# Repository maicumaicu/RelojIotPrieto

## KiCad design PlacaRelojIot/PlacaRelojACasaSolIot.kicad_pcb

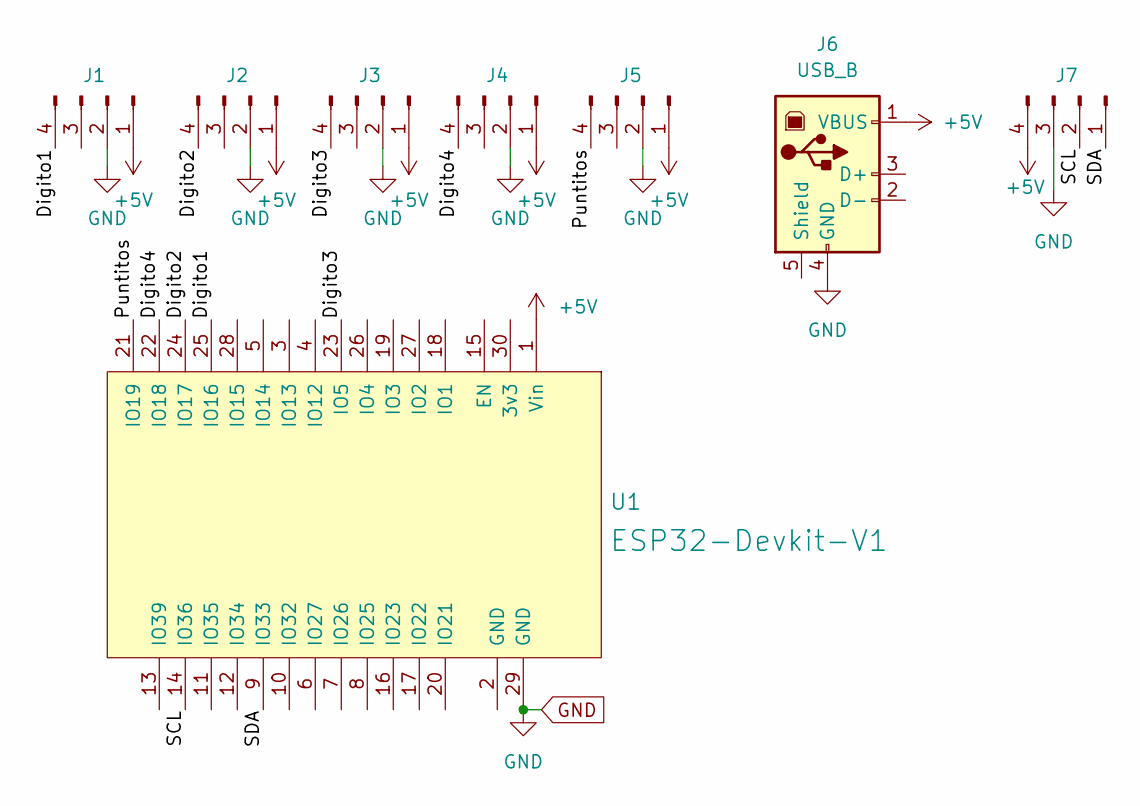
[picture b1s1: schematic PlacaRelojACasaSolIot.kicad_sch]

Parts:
J1, J2, J3, J4, J5, J7: Conn_01x04_Male; FanPinHeader_1x04_P2.54mm_Vertical
J6: USB_B; USB_B_Lumberg_2411_02_Horizontal
U1: ESP32-Devkit-V1; DOIT_ESP32_Devkit

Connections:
+5V: J1.1, J2.1, J3.1, J4.1, J5.1, J6.1 (VBUS), J7.4, U1.1 (Vin)
/Digito1: J1.4, U1.25 (IO16)
/Digito2: J2.4, U1.24 (IO17)
/Digito3: J3.4, U1.23 (IO5)
/Digito4: J4.4, U1.22 (IO18)
/Puntitos: J5.4, U1.21 (IO19)
/SCL: J7.2, U1.14 (IO36)
/SDA: J7.1, U1.9 (IO33)
GND: J1.2, J2.2, J3.2, J4.2, J5.2, J6.4 (GND), J7.3, U1.29 (GND)

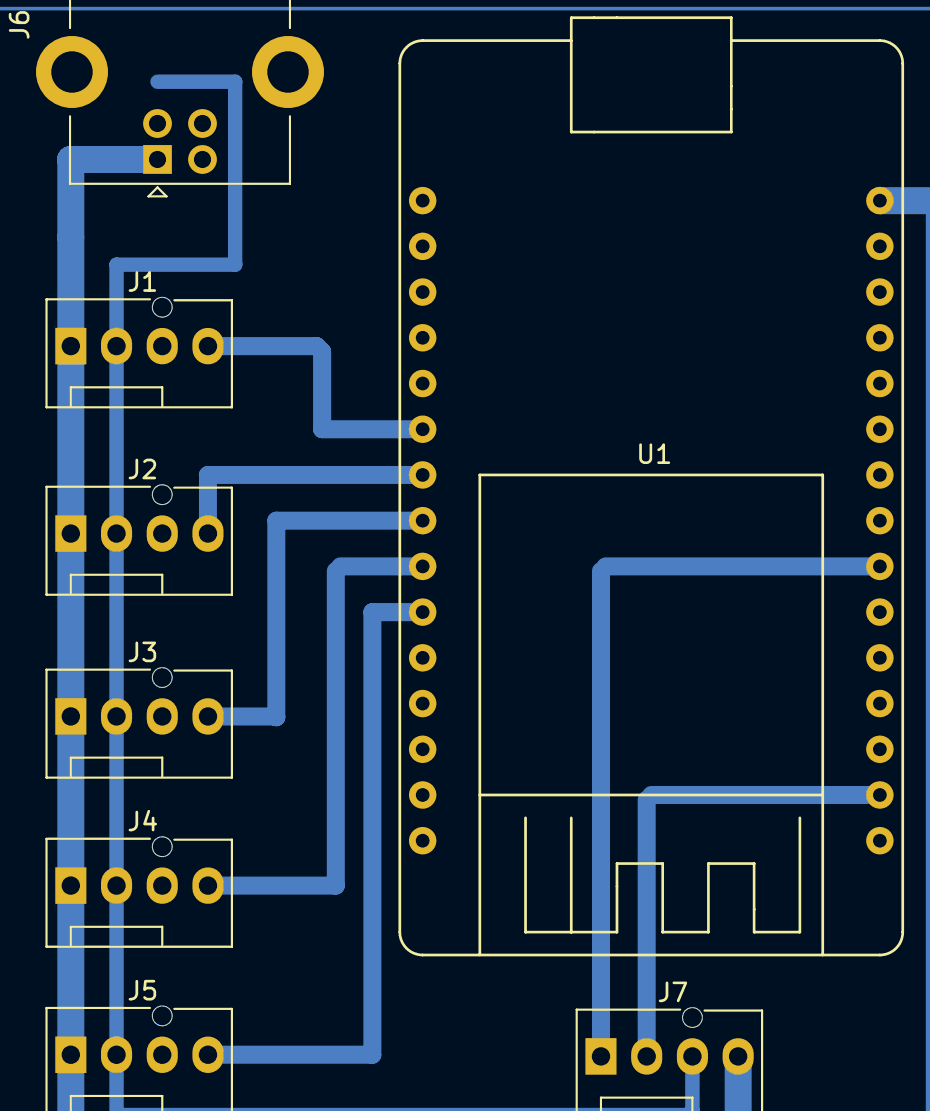
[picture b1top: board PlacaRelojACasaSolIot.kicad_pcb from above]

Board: 2 copper layers, 8 parts (0 on the bottom side), 9 nets.

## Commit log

2022-05-13 cambio nombres
2022-05-14 agrego sensor de temperatura y telegram al rejos
2022-05-16 para zenobi porque bueno
